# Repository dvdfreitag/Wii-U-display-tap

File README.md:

# Wii-U-display-tap
Inline Wii U display tap for probing and injection

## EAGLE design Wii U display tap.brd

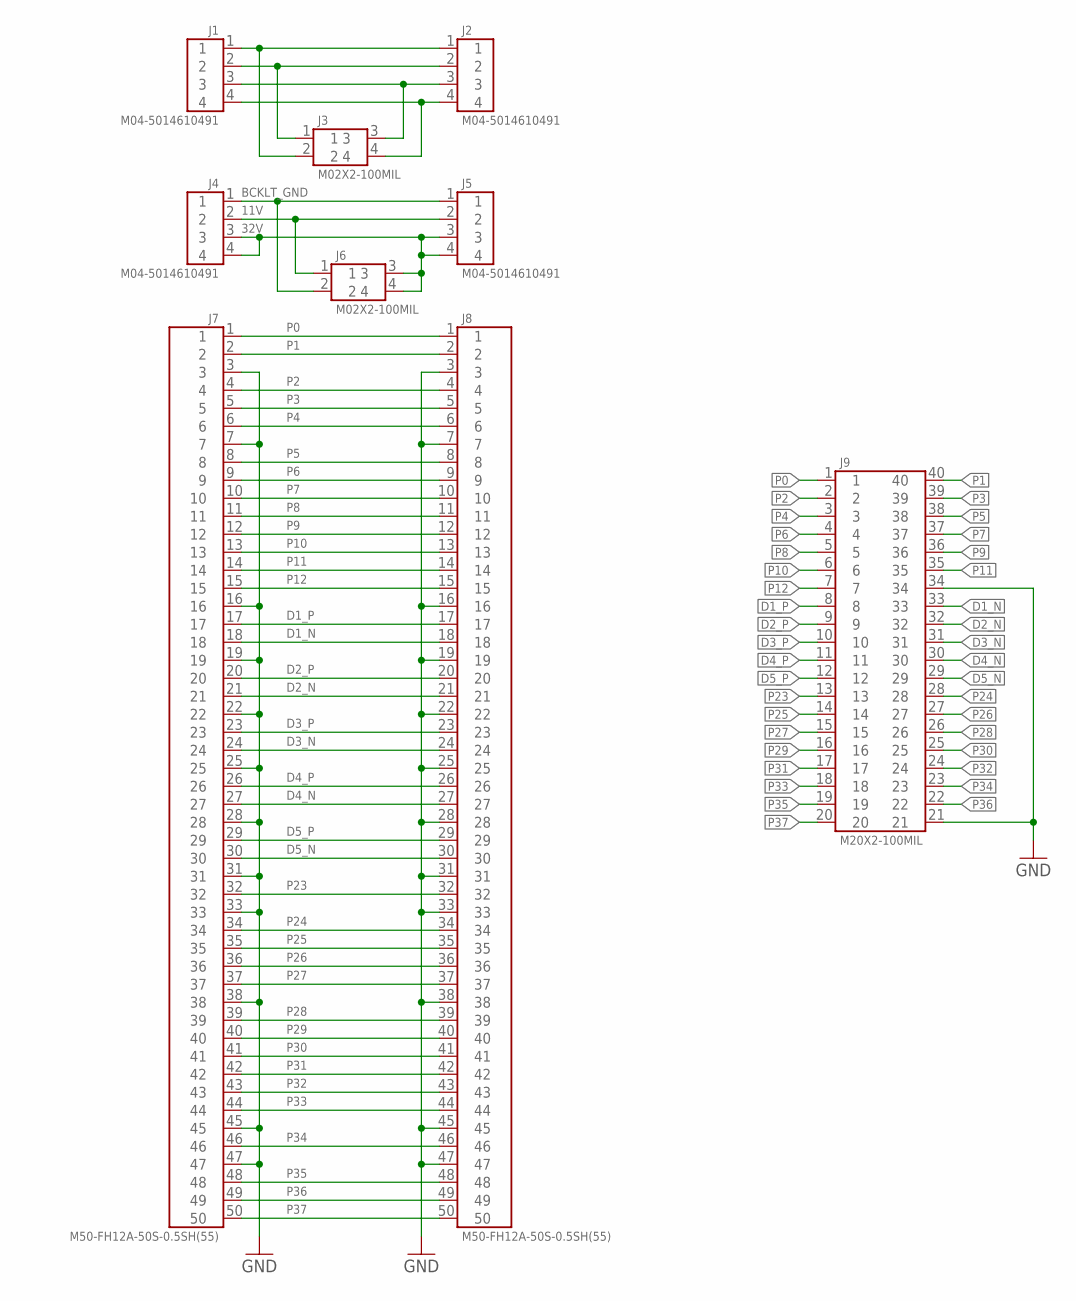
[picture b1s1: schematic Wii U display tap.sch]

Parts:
J1, J2, J4, J5: M04-5014610491; 5014610491
J3, J6: M02X2-100MIL
J7, J8: M50-FH12A-50S-0.5SH(55); FH12A-50S-0.5SH(55)
J9: M20X2-100MIL

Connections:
11V: J4.2, J5.2, J6.1
32V: J4.3, J4.4, J5.3, J5.4, J6.3, J6.4
BCKLT_GND: J4.1, J5.1, J6.2
D1_N: J7.18, J8.18, J9.33
D1_P: J7.17, J8.17, J9.8
D2_N: J7.21, J8.21, J9.32
D2_P: J7.20, J8.20, J9.9
D3_N: J7.24, J8.24, J9.31
D3_P: J7.23, J8.23, J9.10
D4_N: J7.27, J8.27, J9.30
D4_P: J7.26, J8.26, J9.11
D5_N: J7.30, J8.30, J9.29
D5_P: J7.29, J8.29, J9.12
GND: J7.3, J7.7, J7.16, J7.19, J7.22, J7.25, J7.28, J7.31, J7.33, J7.38, J7.45, J7.47, J8.3, J8.7, J8.16, J8.19, J8.22, J8.25, J8.28, J8.31, J8.33, J8.38, J8.45, J8.47, J9.21, J9.34
unnamed: J1.3, J2.3, J3.3
unnamed: J1.4, J2.4, J3.4
unnamed: J1.2, J2.2, J3.1
unnamed: J1.1, J2.1, J3.2
P0: J7.1, J8.1, J9.1
P1: J7.2, J8.2, J9.40
P2: J7.4, J8.4, J9.2
P3: J7.5, J8.5, J9.39
P4: J7.6, J8.6, J9.3
P5: J7.8, J8.8, J9.38
P6: J7.9, J8.9, J9.4
P7: J7.10, J8.10, J9.37
P8: J7.11, J8.11, J9.5
P9: J7.12, J8.12, J9.36
P10: J7.13, J8.13, J9.6
P11: J7.14, J8.14, J9.35
P12: J7.15, J8.15, J9.7
P23: J7.32, J8.32, J9.13
P24: J7.34, J8.34, J9.28
P25: J7.35, J8.35, J9.14
P26: J7.36, J8.36, J9.27
P27: J7.37, J8.37, J9.15
P28: J7.39, J8.39, J9.26
P29: J7.40, J8.40, J9.16
P30: J7.41, J8.41, J9.25
P31: J7.42, J8.42, J9.17
P32: J7.43, J8.43, J9.24
P33: J7.44, J8.44, J9.18
P34: J7.46, J8.46, J9.23
P35: J7.48, J8.48, J9.19
P36: J7.49, J8.49, J9.22
P37: J7.50, J8.50, J9.20

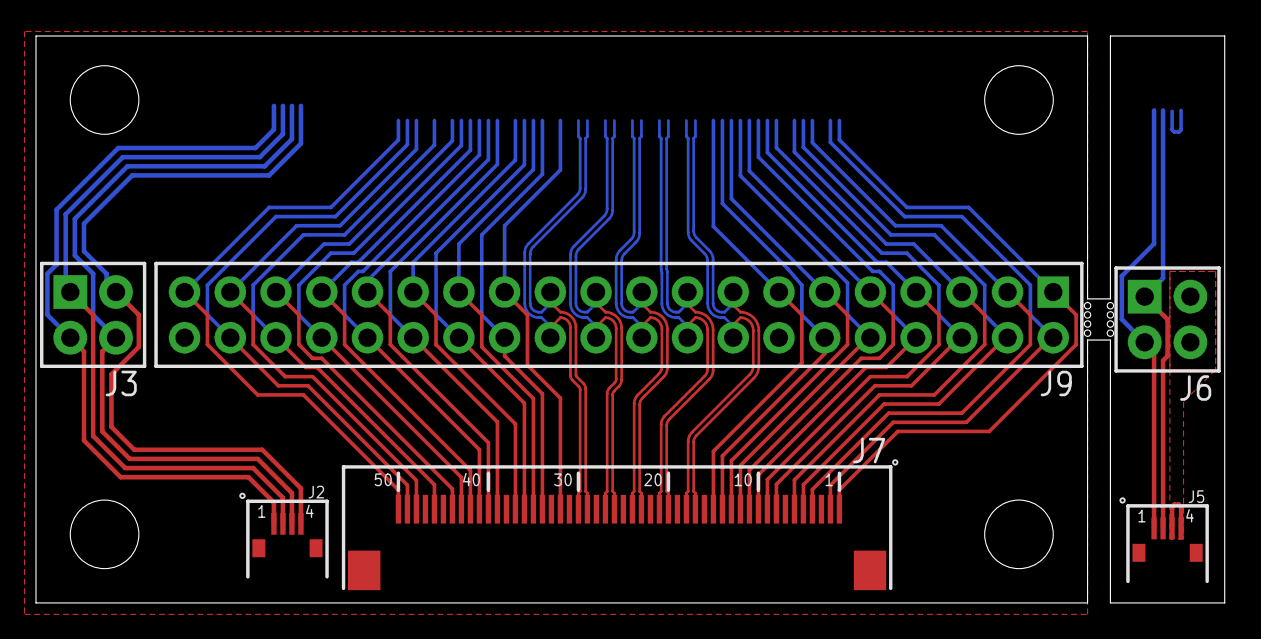
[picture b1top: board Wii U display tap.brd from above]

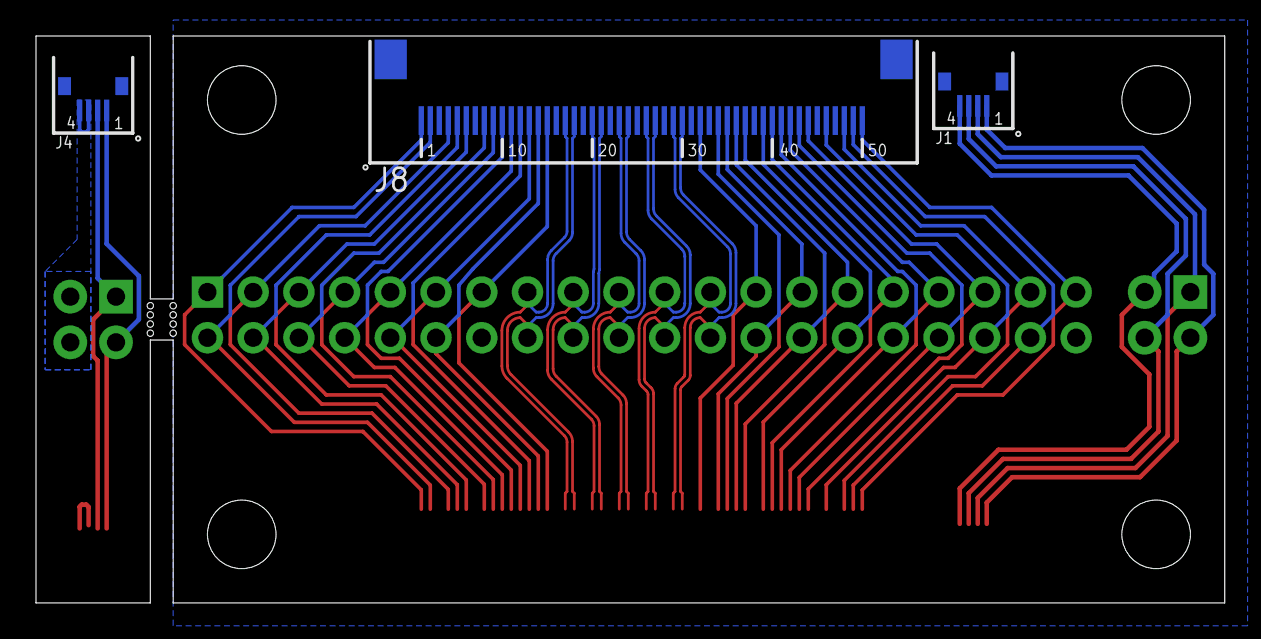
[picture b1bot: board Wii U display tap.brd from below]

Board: 2 copper layers, 66.0 x 31.5 mm, 9 parts (3 on the bottom side), 46 nets.

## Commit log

2018-02-07 :octocat: Added .gitattributes & .gitignore files
2018-02-07 Create LICENSE
